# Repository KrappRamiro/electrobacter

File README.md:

# Electrobacter

Para los que no usen kicad, solamente les interesan estos archivos:

## esquematico.pdf
Tiene el esquematico del proyecto

## placa_cobre.pdf
Tiene la parte que va planchada al cobre

## silkscreen.pdf

Tiene la parte que va en el frente, o sea, donde va los componentes.
Eso vos lo planchas y despues a la hora de colocar los componentes,
te ayuda a saber cuál es cual.

## placa_3D.png

Tiene una vista 3D de la placa, esta lindo :)

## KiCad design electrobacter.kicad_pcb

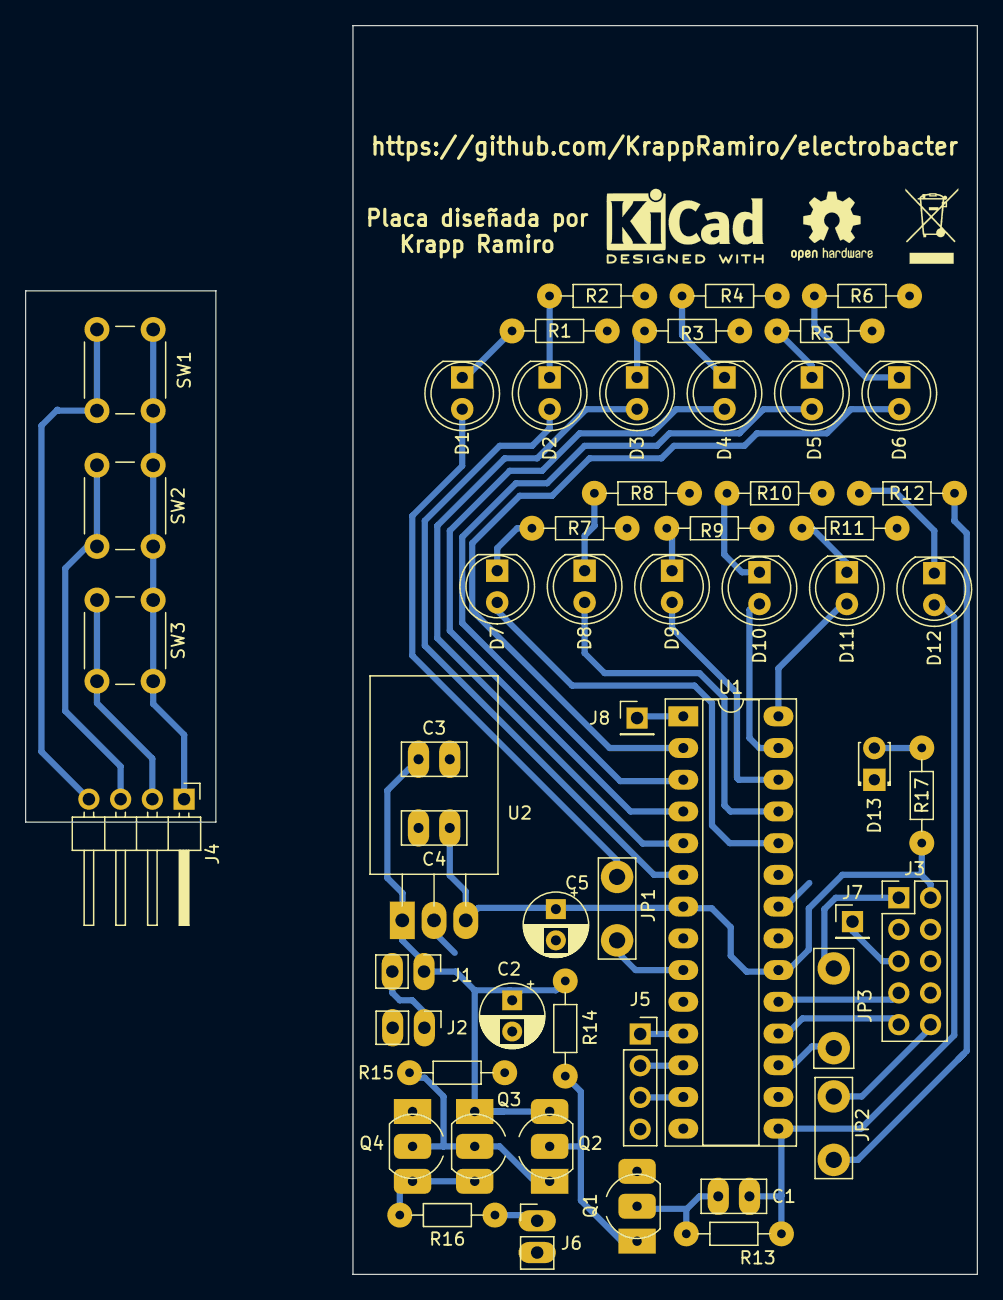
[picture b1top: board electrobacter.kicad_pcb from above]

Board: 2 copper layers, 76.2 x 100.0 mm, 55 parts (0 on the bottom side), 46 nets.

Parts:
C1: 10nF; cap-disco-chico-pads-grandes
C2: 100uF; CP_Radial_D5.0mm_P2.50mm
C3, C4: 100nF; cap-disco-chico-pads-grandes
C5: 10uF; CP_Radial_D5.0mm_P2.50mm
D1, D2, D3, D4, D5, D6, D7, D8, D9, D10, D11, D12: LED; LED_D5.0mm
D13: LED; LED_D1.8mm_W3.3mm_H2.4mm
J1: CONN_switch; PinHeader_1x02_P2.54mm_Vertical
J2: CONN_Bateria; Pin-macho-arduino-2x1-pads-grandes
J3: CONN_programador; PinHeader_2x05_P2.54mm_Vertical
J4: Conn_01x04_Male; PinHeader_1x04_P2.54mm_Horizontal
J5: CONN_botones; PinSocket_1x04_P2.54mm_Vertical
J6: CONN_OUT; Pin-macho-arduino-2x1-pads-grandes
J7, J8: conn_reset; PinHeader_1x01_P2.54mm_Vertical
JP1, JP2: Jumper_2_Bridged; TestPoint_Bridge_Pitch5.08mm_Drill1.3mm
JP3: Jumper_2_Bridged; TestPoint_Bridge_Pitch6.35mm_Drill1.3mm
Q1: BC547; krapp-TO-92_HandSolder
Q2, Q4: BC327; krapp-TO-92_HandSolder
Q3: BC337; krapp-TO-92_HandSolder
R1, R2, R3, R4, R5, R6, R7, R8, R9, R10, R11, R12, R17: 1k; krapp-res-generic
R13: 2.2K; krapp-res-generic
R14, R15: 470; krapp-res-generic
R16: 100; krapp-res-generic
SW1, SW2, SW3: SW_Push; SW_PUSH_6mm
U1: ATmega48V-10P; DIP-28_W7.62mm_Socket_LongPads
U2: L7805; TO-220-horizontal-pads-grandes

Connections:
+5V: C4.1, C5.1, J3.2, R17.1, U1.7 (VCC), U1.20 (AVCC), U2.3 (OUT)
+9V: C2.1, C3.1, J1.1, Q2.3 (E), Q3.1 (C), R14.2, U2.1 (IN)
/btn1: J4.4, SW1.2
/btn2: J4.3, SW2.2
/btn3: J4.2, SW3.2
/btn-gnd: J4.1, SW1.1, SW2.1, SW3.1
/led1: D1.2 (A), JP1.1 (A), U1.9 (XTAL1/PB6)
/led2: D2.2 (A), U1.6 (PD4)
/led3: D3.2 (A), U1.5 (PD3)
/led4: D4.2 (A), U1.4 (PD2)
/led5: D5.2 (A), U1.3 (PD1)
/led6: D6.2 (A), U1.2 (PD0)
/led7: D7.2 (A), U1.24 (PC1)
/led8: D8.2 (A), U1.25 (PC2)
/led9: D9.2 (A), U1.26 (PC3)
/led10: D10.2 (A), U1.27 (PC4)
/led11: D11.2 (A), U1.28 (PC5)
/miso: J3.9, U1.18 (PB4)
/mosi: J3.1, JP3.1 (A), U1.17 (PB3)
/out+: J6.1, R16.1
/pwm: C1.1, D12.2 (A), R13.1, U1.15 (PB1)
/sck: J3.7, U1.19 (PB5)
GND: C2.2, C3.2, C4.2, C5.2, D13.1 (K), J2.2, J3.10, J5.4, J6.2, JP2.1 (A), Q1.3 (E), Q4.1 (C), R1.1, R2.1, R3.1, R4.1, R5.1, R6.1, R7.1, R8.1, R9.1, R10.1, R11.1, R12.1, R15.1, U1.8 (GND), U1.22 (GND), U2.2 (GND)
unnamed: J1.2, J2.1
unnamed: C1.2, Q1.2 (B), R13.2
unnamed: D1.1 (K), R1.2
unnamed: D2.1 (K), R2.2
unnamed: D3.1 (K), R3.2
unnamed: D4.1 (K), R4.2
unnamed: D5.1 (K), R5.2
unnamed: D6.1 (K), R6.2
unnamed: D7.1 (K), R7.2
unnamed: D8.1 (K), R8.2
unnamed: D9.1 (K), R9.2
unnamed: D10.1 (K), R10.2
unnamed: D11.1 (K), R11.2
unnamed: D12.1 (K), R12.2
unnamed: D13.2 (A), R17.2
unnamed: J3.5, J7.1
unnamed: J5.1, U1.11 (PD5)
unnamed: J5.2, U1.12 (PD6)
unnamed: J5.3, U1.13 (PD7)
unnamed: J8.1, U1.1 (~RESET/PC6)
unnamed: Q1.1 (C), Q2.2 (B), R14.1
unnamed: Q2.1 (C), Q3.2 (B), Q4.2 (B), R15.2
unnamed: Q3.3 (E), Q4.3 (E), R16.2

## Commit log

2022-05-26 armado esquematico y pcb
2022-05-26 añadidos pdfs y hechos pequeños cambios esteticos en la placa
2022-05-26 añadido readme
2022-05-27 añadido archivo para imprimir
